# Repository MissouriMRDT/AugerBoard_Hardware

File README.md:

# AugerBoard_Hardware
KiCAD design files for Auger motion control board.

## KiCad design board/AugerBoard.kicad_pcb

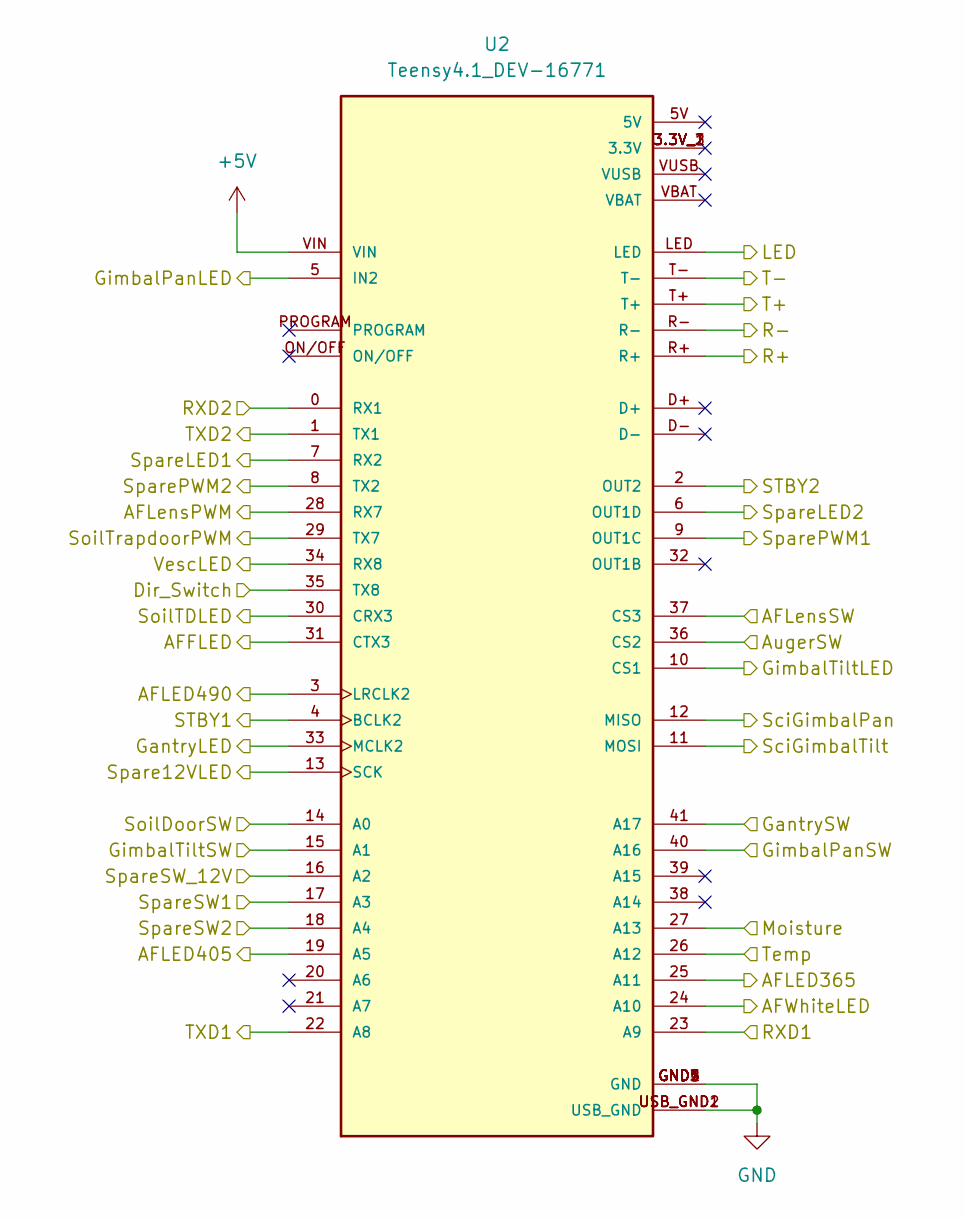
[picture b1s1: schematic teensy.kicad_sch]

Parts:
U2: Teensy4.1_DEV-16771; Teensy_4_1_Ethernet; PARTREV 4.1

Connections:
+5V: U2.VIN; also elsewhere on the board
/AF interface/AFLED365: U2.25 (A11); also elsewhere on the board
/AF interface/AFLED405: U2.19 (A5); also elsewhere on the board
/AF interface/AFLED490: U2.3 (LRCLK2); also elsewhere on the board
/AF interface/AFWhiteLED: U2.24 (A10); also elsewhere on the board
/Communications/LED: U2.LED; also elsewhere on the board
/Communications/R+: U2.R+; also elsewhere on the board
/Communications/R-: U2.R-; also elsewhere on the board
/Communications/RXD1: U2.23 (A9); also elsewhere on the board
/Communications/RXD2: U2.0 (RX1); also elsewhere on the board
/Communications/STBY1: U2.4 (BCLK2); also elsewhere on the board
/Communications/STBY2: U2.2 (OUT2); also elsewhere on the board
/Communications/T+: U2.T+; also elsewhere on the board
/Communications/T-: U2.T-; also elsewhere on the board
/Communications/TXD1: U2.22 (A8); also elsewhere on the board
/Communications/TXD2: U2.1 (TX1); also elsewhere on the board
/Power/AFFLED: U2.31 (CTX3); also elsewhere on the board
/Power/GantryLED: U2.33 (MCLK2); also elsewhere on the board
/Power/GimbalPanLED: U2.5 (IN2); also elsewhere on the board
/Power/GimbalTiltLED: U2.10 (CS1); also elsewhere on the board
/Power/SoilTDLED: U2.30 (CRX3); also elsewhere on the board
/Power/Spare12VLED: U2.13 (SCK); also elsewhere on the board
/Power/SpareLED1: U2.7 (RX2); also elsewhere on the board
/Power/SpareLED2: U2.6 (OUT1D); also elsewhere on the board
/Power/VescLED: U2.34 (RX8); also elsewhere on the board
/Servos/AFLensPWM: U2.28 (RX7); also elsewhere on the board
/Servos/SciGimbalPan: U2.12 (MISO); also elsewhere on the board
/Servos/SciGimbalTilt: U2.11 (MOSI); also elsewhere on the board
/Servos/SoilTrapdoorPWM: U2.29 (TX7); also elsewhere on the board
/Servos/SparePWM1: U2.9 (OUT1C); also elsewhere on the board
/Servos/SparePWM2: U2.8 (TX2); also elsewhere on the board
/Soil Sensors/Moisture: U2.27 (A13); also elsewhere on the board
/Soil Sensors/Temp: U2.26 (A12); also elsewhere on the board
/Teensy/AFLensSW: U2.37 (CS3); also elsewhere on the board
/Teensy/AugerSW: U2.36 (CS2); also elsewhere on the board
/Teensy/Dir_Switch: U2.35 (TX8); also elsewhere on the board
/Teensy/GantrySW: U2.41 (A17); also elsewhere on the board
/Teensy/GimbalPanSW: U2.40 (A16); also elsewhere on the board
/Teensy/GimbalTiltSW: U2.15 (A1); also elsewhere on the board
/Teensy/SoilDoorSW: U2.14 (A0); also elsewhere on the board
/Teensy/SpareSW1: U2.17 (A3); also elsewhere on the board
/Teensy/SpareSW2: U2.18 (A4); also elsewhere on the board
/Teensy/SpareSW_12V: U2.16 (A2); also elsewhere on the board
GND: U2.GND1 (GND), U2.GND2 (GND), U2.GND3 (GND), U2.GND4 (GND), U2.GND5 (GND), U2.USB_GND1 (USB_GND), U2.USB_GND2 (USB_GND); also elsewhere on the board

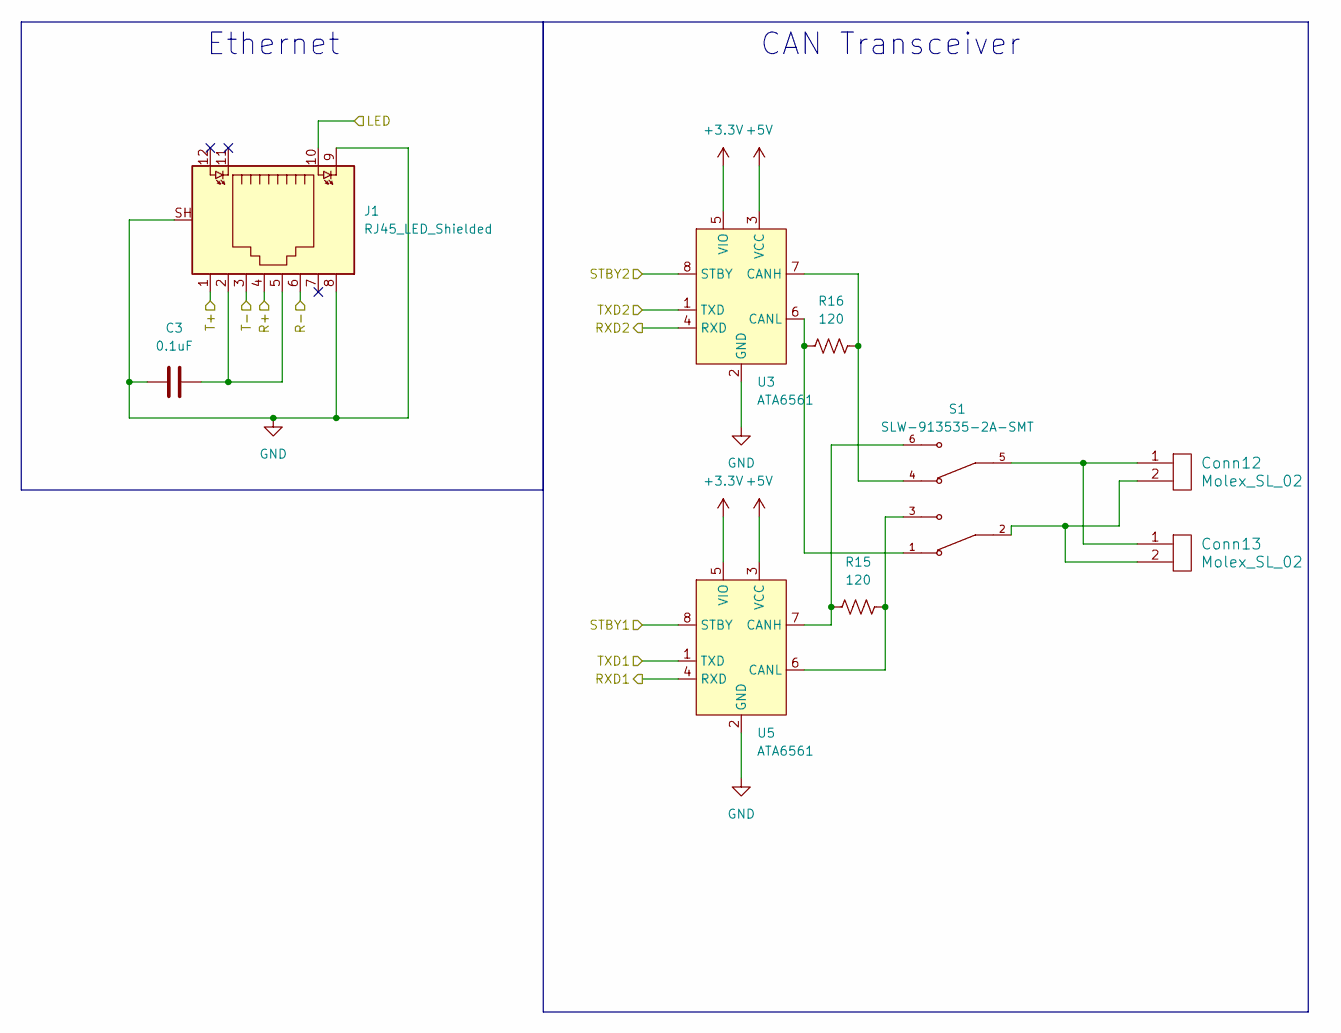
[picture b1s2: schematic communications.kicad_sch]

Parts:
C3: 0.1uF; C_0603_1608Metric_Pad1.08x0.95mm_HandSolder
Conn12, Conn13: Molex_SL_02; MOLEX_SL_02_Vertical
J1: RJ45_LED_Shielded; RJ45_Teensy
R15, R16: 120; R_0603_1608Metric_Pad0.98x0.95mm_HandSolder
S1: SLW-913535-2A-SMT; SW_SLW-913535-2A-SMT; PARTREV 1.01
U3, U5: ATA6561; SOIC-8_3.9x4.9mm_P1.27mm

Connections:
+3.3V: U3.5 (VIO), U5.5 (VIO); also elsewhere on the board
+5V: U3.3 (VCC), U5.3 (VCC); also elsewhere on the board
/Communications/LED: J1.10; also elsewhere on the board
/Communications/R+: J1.4; also elsewhere on the board
/Communications/R-: J1.6; also elsewhere on the board
/Communications/RXD1: U5.4 (RXD); also elsewhere on the board
/Communications/RXD2: U3.4 (RXD); also elsewhere on the board
/Communications/STBY1: U5.8 (STBY); also elsewhere on the board
/Communications/STBY2: U3.8 (STBY); also elsewhere on the board
/Communications/T+: J1.1; also elsewhere on the board
/Communications/T-: J1.3; also elsewhere on the board
/Communications/TXD1: U5.1 (TXD); also elsewhere on the board
/Communications/TXD2: U3.1 (TXD); also elsewhere on the board
GND: C3.1, J1.8, J1.9, J1.SH, U3.2 (GND), U5.2 (GND); also elsewhere on the board
unnamed: C3.2, J1.2, J1.5
unnamed: Conn12.1, Conn13.1, S1.5
unnamed: Conn12.2, Conn13.2, S1.2
unnamed: R16.1, S1.4, U3.7 (CANH)
unnamed: R16.2, S1.1, U3.6 (CANL)
unnamed: R15.2, S1.6, U5.7 (CANH)
unnamed: R15.1, S1.3, U5.6 (CANL)

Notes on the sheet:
Ethernet
CAN Transceiver

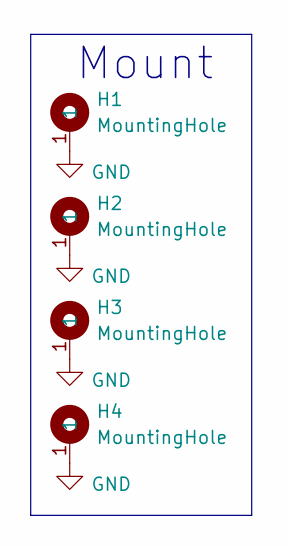
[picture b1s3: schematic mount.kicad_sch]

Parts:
H1, H2, H3, H4: MountingHole; 4_40_Hole_Pad_Via

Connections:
GND: H1.1, H2.1, H3.1, H4.1; also elsewhere on the board

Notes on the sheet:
Mount

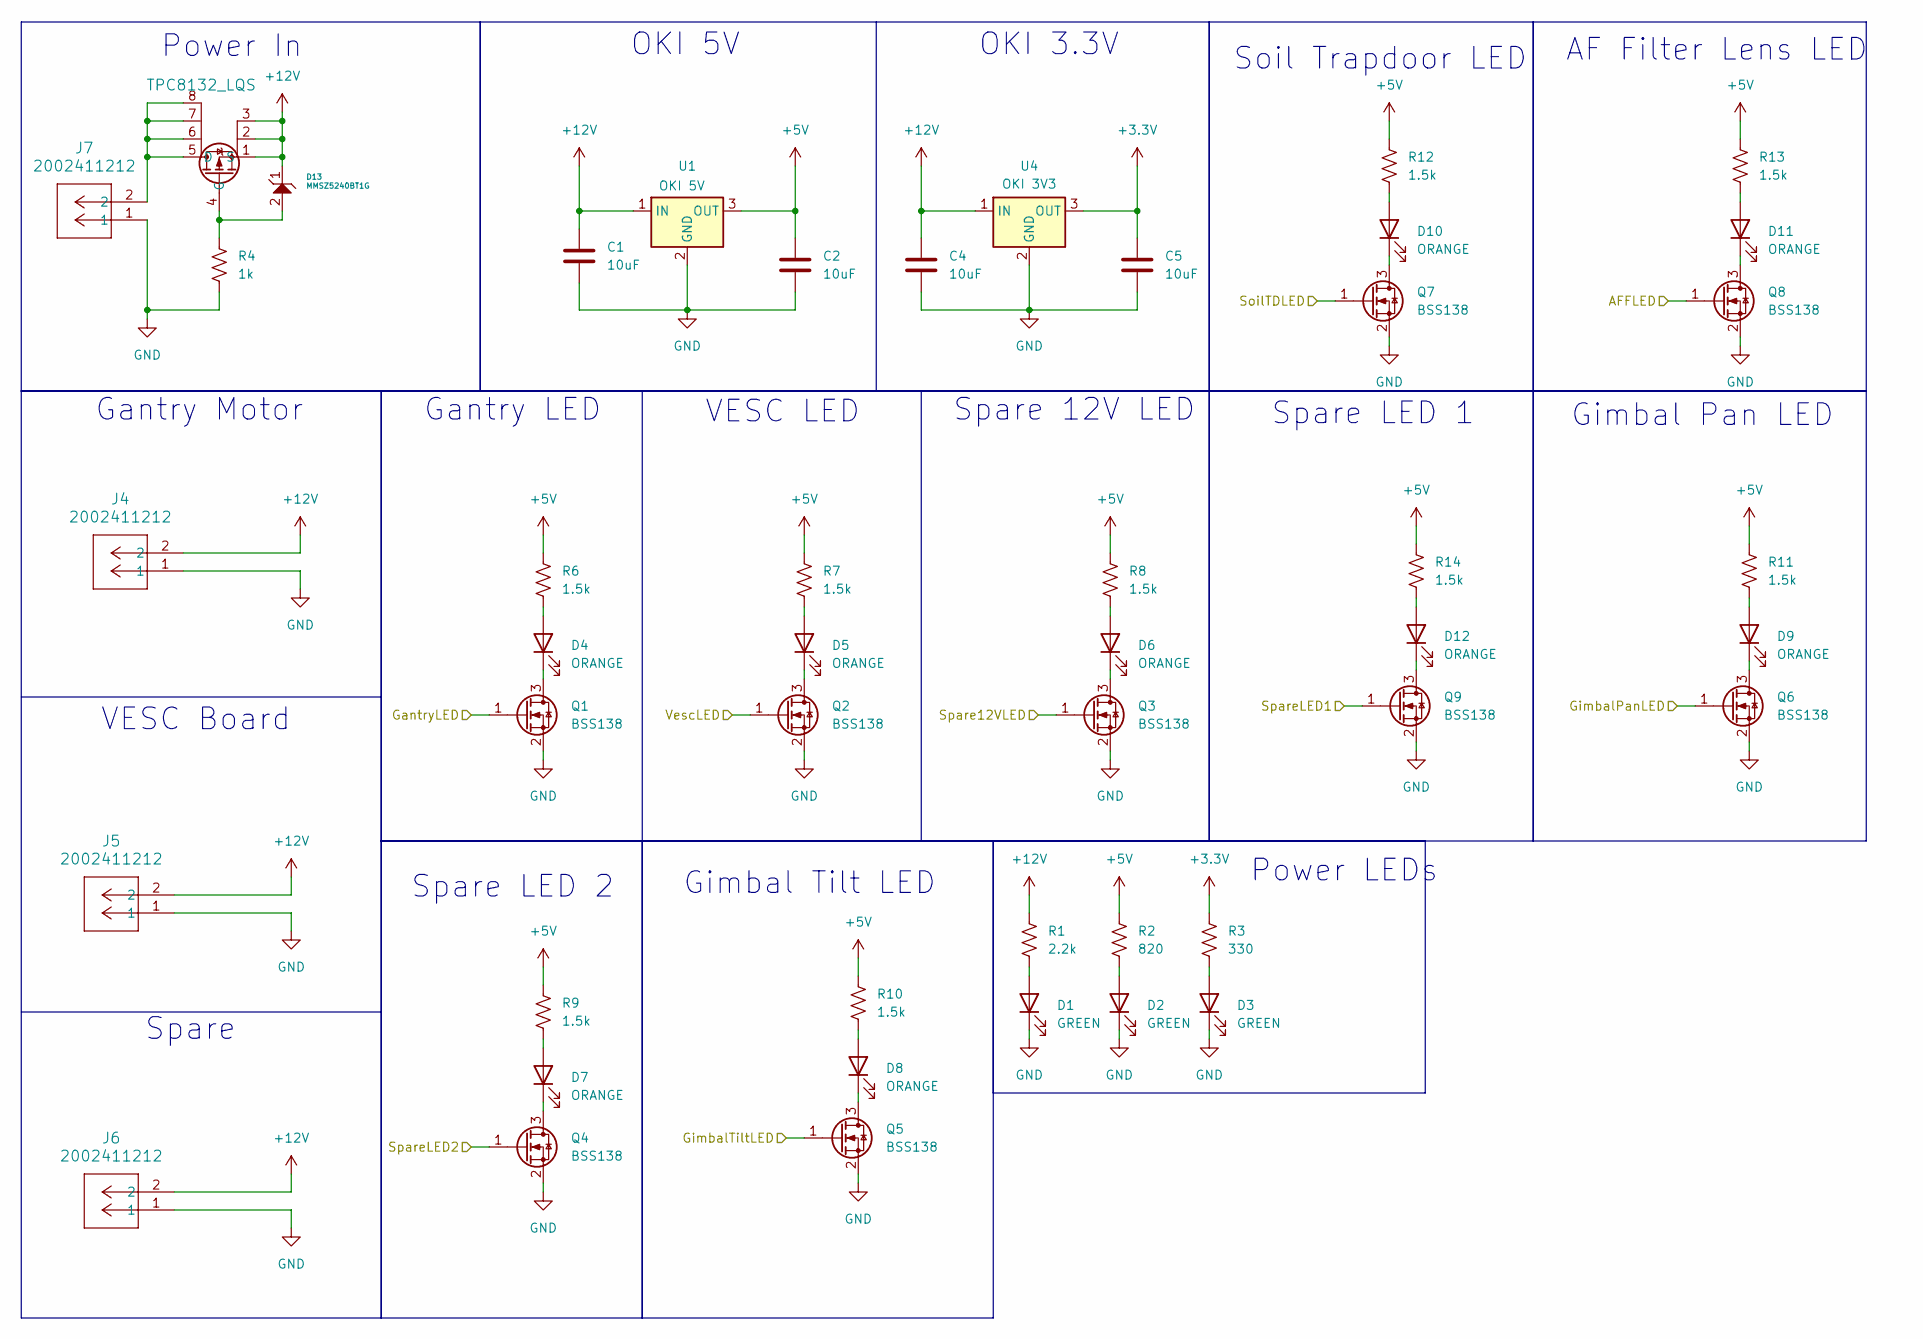
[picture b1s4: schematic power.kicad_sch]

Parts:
C1, C2, C4, C5: 10uF; C_0603_1608Metric_Pad1.08x0.95mm_HandSolder
D1, D2, D3: GREEN; LED_0603_1608Metric_Pad1.05x0.95mm_HandSolder
D4, D5, D6, D7, D8, D9, D10, D11, D12: ORANGE; LED_0603_1608Metric_Pad1.05x0.95mm_HandSolder
D13: MMSZ5240BT1G; SOD-123_ONS-L
J4, J5, J6, J7: 2002411212; CONN_SD-76825-0100_02_MOL
MOSFET1: TPC8132_LQS; SOP-8_TOS-L
Q1, Q2, Q3, Q4, Q5, Q6, Q7, Q8, Q9: BSS138; SOT-23
R1: 2.2k; R_0603_1608Metric_Pad0.98x0.95mm_HandSolder
R2: 820; R_0603_1608Metric_Pad0.98x0.95mm_HandSolder
R3: 330; R_0603_1608Metric_Pad0.98x0.95mm_HandSolder
R4: 1k; R_0603_1608Metric_Pad0.98x0.95mm_HandSolder
R6, R7, R8, R9, R10, R11, R12, R13, R14: 1.5k; R_0603_1608Metric_Pad0.98x0.95mm_HandSolder
U1: OKI 5V; OKI_Horizontal
U4: OKI 3V3; OKI_Horizontal

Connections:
+3.3V: C5.1, R3.1, U4.3 (OUT); also elsewhere on the board
+5V: C2.1, R2.1, R6.1, R7.1, R8.1, R9.1, R10.1, R11.1, R12.1, R13.1, R14.1, U1.3 (OUT); also elsewhere on the board
+12V: C1.1, C4.1, D13.1, J4.2, J5.2, J6.2, MOSFET1.1 (S), MOSFET1.2, MOSFET1.3, R1.1, U1.1 (IN), U4.1 (IN); also elsewhere on the board
/Power/AFFLED: Q8.1 (G); also elsewhere on the board
/Power/GantryLED: Q1.1 (G); also elsewhere on the board
/Power/GimbalPanLED: Q6.1 (G); also elsewhere on the board
/Power/GimbalTiltLED: Q5.1 (G); also elsewhere on the board
/Power/SoilTDLED: Q7.1 (G); also elsewhere on the board
/Power/Spare12VLED: Q3.1 (G); also elsewhere on the board
/Power/SpareLED1: Q9.1 (G); also elsewhere on the board
/Power/SpareLED2: Q4.1 (G); also elsewhere on the board
/Power/VescLED: Q2.1 (G); also elsewhere on the board
GND: C1.2, C2.2, C4.2, C5.2, D1.1 (K), D2.1 (K), D3.1 (K), J4.1, J5.1, J6.1, J7.1, Q1.2 (S), Q2.2 (S), Q3.2 (S), Q4.2 (S), Q5.2 (S), Q6.2 (S), Q7.2 (S), Q8.2 (S), Q9.2 (S), R4.2, U1.2 (GND), U4.2 (GND); also elsewhere on the board
unnamed: D1.2 (A), R1.2
unnamed: D2.2 (A), R2.2
unnamed: D3.2 (A), R3.2
unnamed: D4.2 (A), R6.2
unnamed: D4.1 (K), Q1.3 (D)
unnamed: D5.2 (A), R7.2
unnamed: D5.1 (K), Q2.3 (D)
unnamed: D6.2 (A), R8.2
unnamed: D6.1 (K), Q3.3 (D)
unnamed: D7.2 (A), R9.2
unnamed: D7.1 (K), Q4.3 (D)
unnamed: D8.2 (A), R10.2
unnamed: D8.1 (K), Q5.3 (D)
unnamed: D9.2 (A), R11.2
unnamed: D9.1 (K), Q6.3 (D)
unnamed: D10.2 (A), R12.2
unnamed: D10.1 (K), Q7.3 (D)
unnamed: D11.2 (A), R13.2
unnamed: D11.1 (K), Q8.3 (D)
unnamed: D12.2 (A), R14.2
unnamed: D12.1 (K), Q9.3 (D)
unnamed: J7.2, MOSFET1.5 (D), MOSFET1.6, MOSFET1.7, MOSFET1.8
unnamed: D13.2, MOSFET1.4 (G), R4.1

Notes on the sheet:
Power In
Spare 12V LED
VESC LED
Gimbal Tilt LED
Spare LED 1
OKI 3.3V
Gantry Motor
AF Filter Lens LED
Power LEDs
Spare LED 2
Gantry LED
Soil Trapdoor LED
Gimbal Pan LED
OKI 5V
Spare
VESC Board

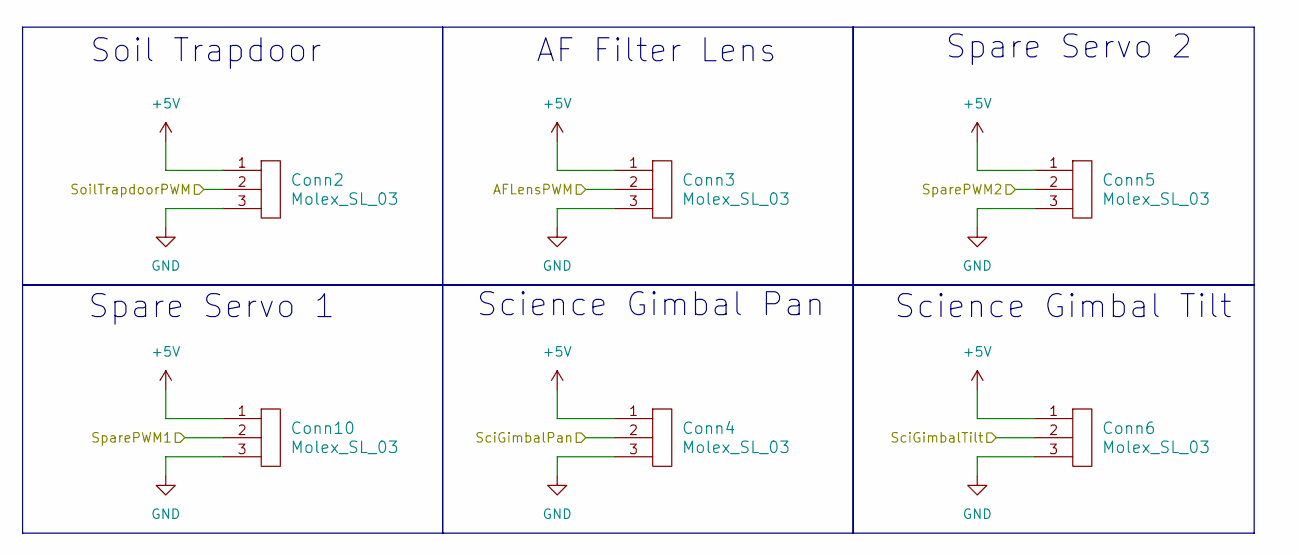
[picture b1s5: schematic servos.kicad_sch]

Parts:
Conn2, Conn3, Conn4, Conn5, Conn6, Conn10: Molex_SL_03; MOLEX_SL_03_Vertical

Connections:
+5V: Conn2.1, Conn3.1, Conn4.1, Conn5.1, Conn6.1, Conn10.1; also elsewhere on the board
/Servos/AFLensPWM: Conn3.2; also elsewhere on the board
/Servos/SciGimbalPan: Conn4.2; also elsewhere on the board
/Servos/SciGimbalTilt: Conn6.2; also elsewhere on the board
/Servos/SoilTrapdoorPWM: Conn2.2; also elsewhere on the board
/Servos/SparePWM1: Conn10.2; also elsewhere on the board
/Servos/SparePWM2: Conn5.2; also elsewhere on the board
GND: Conn2.3, Conn3.3, Conn4.3, Conn5.3, Conn6.3, Conn10.3; also elsewhere on the board

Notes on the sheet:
AF Filter Lens
Soil Trapdoor
Spare Servo 1
Spare Servo 2
Science Gimbal Pan
Science Gimbal Tilt

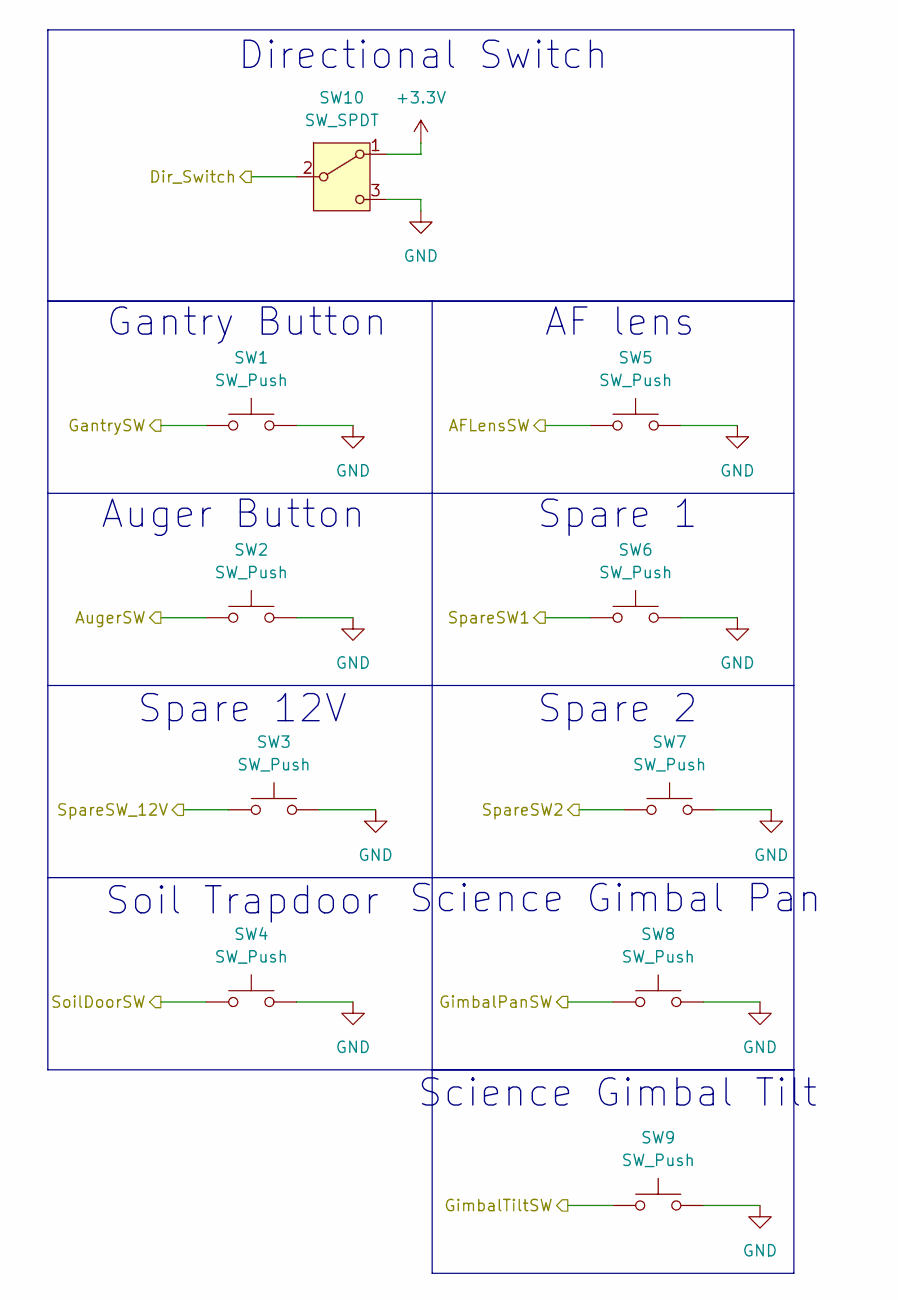
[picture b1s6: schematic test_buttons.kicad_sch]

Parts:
SW1, SW2, SW3, SW4, SW5, SW6, SW7, SW8, SW9: SW_Push; SW_SPST_TL3305A
SW10: SW_SPDT; SW_Slide_SPDT_Straight_CK_OS102011MS2Q

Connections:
+3.3V: SW10.1 (A); also elsewhere on the board
/Teensy/AFLensSW: SW5.1; also elsewhere on the board
/Teensy/AugerSW: SW2.1; also elsewhere on the board
/Teensy/Dir_Switch: SW10.2 (B); also elsewhere on the board
/Teensy/GantrySW: SW1.1; also elsewhere on the board
/Teensy/GimbalPanSW: SW8.1; also elsewhere on the board
/Teensy/GimbalTiltSW: SW9.1; also elsewhere on the board
/Teensy/SoilDoorSW: SW4.1; also elsewhere on the board
/Teensy/SpareSW1: SW6.1; also elsewhere on the board
/Teensy/SpareSW2: SW7.1; also elsewhere on the board
/Teensy/SpareSW_12V: SW3.1; also elsewhere on the board
GND: SW1.2, SW2.2, SW3.2, SW4.2, SW5.2, SW6.2, SW7.2, SW8.2, SW9.2, SW10.3 (C); also elsewhere on the board

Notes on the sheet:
Spare 2
Spare 1
Directional Switch
Gantry Button
Auger Button
Spare 12V
Science Gimbal Pan
AF lens
Soil Trapdoor
Science Gimbal Tilt

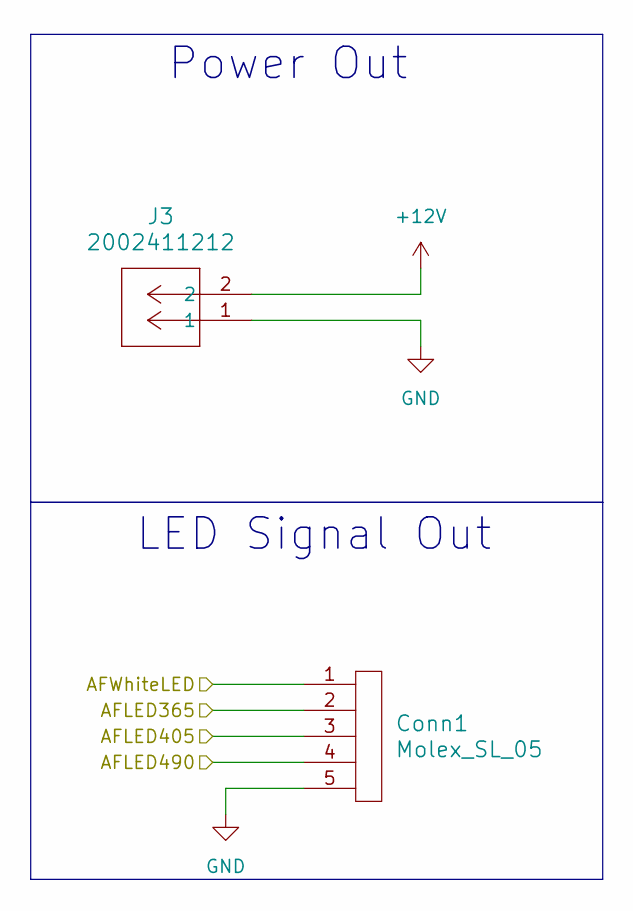
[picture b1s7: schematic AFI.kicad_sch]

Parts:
Conn1: Molex_SL_05; MOLEX_SL_05_Vertical
J3: 2002411212; CONN_SD-76825-0100_02_MOL

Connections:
+12V: J3.2; also elsewhere on the board
/AF interface/AFLED365: Conn1.2; also elsewhere on the board
/AF interface/AFLED405: Conn1.3; also elsewhere on the board
/AF interface/AFLED490: Conn1.4; also elsewhere on the board
/AF interface/AFWhiteLED: Conn1.1; also elsewhere on the board
GND: Conn1.5, J3.1; also elsewhere on the board

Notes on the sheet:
LED Signal Out
Power Out

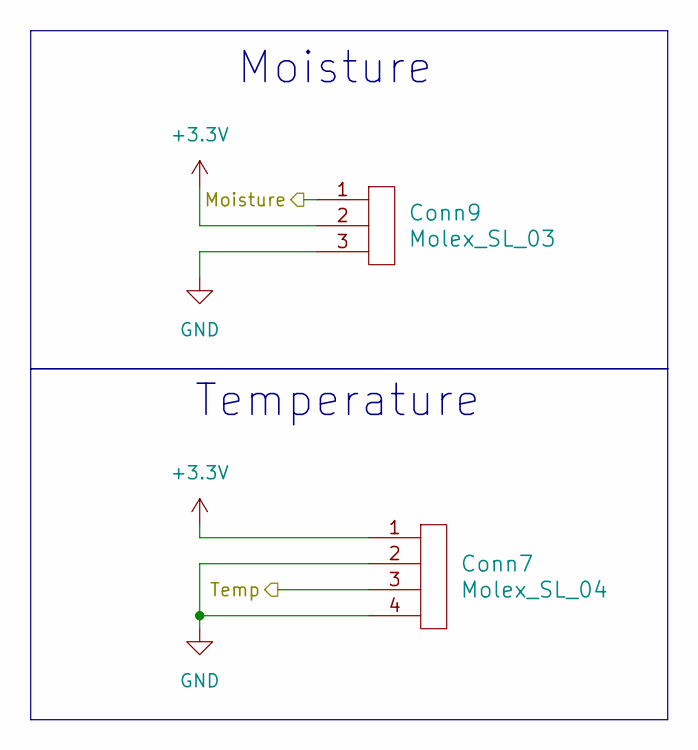
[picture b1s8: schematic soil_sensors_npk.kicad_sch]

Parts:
Conn7: Molex_SL_04; MOLEX_SL_04_Vertical
Conn9: Molex_SL_03; MOLEX_SL_03_Vertical

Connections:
+3.3V: Conn7.1, Conn9.2; also elsewhere on the board
/Soil Sensors/Moisture: Conn9.1; also elsewhere on the board
/Soil Sensors/Temp: Conn7.3; also elsewhere on the board
GND: Conn7.2, Conn7.4, Conn9.3; also elsewhere on the board

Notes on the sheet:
Moisture
Temperature

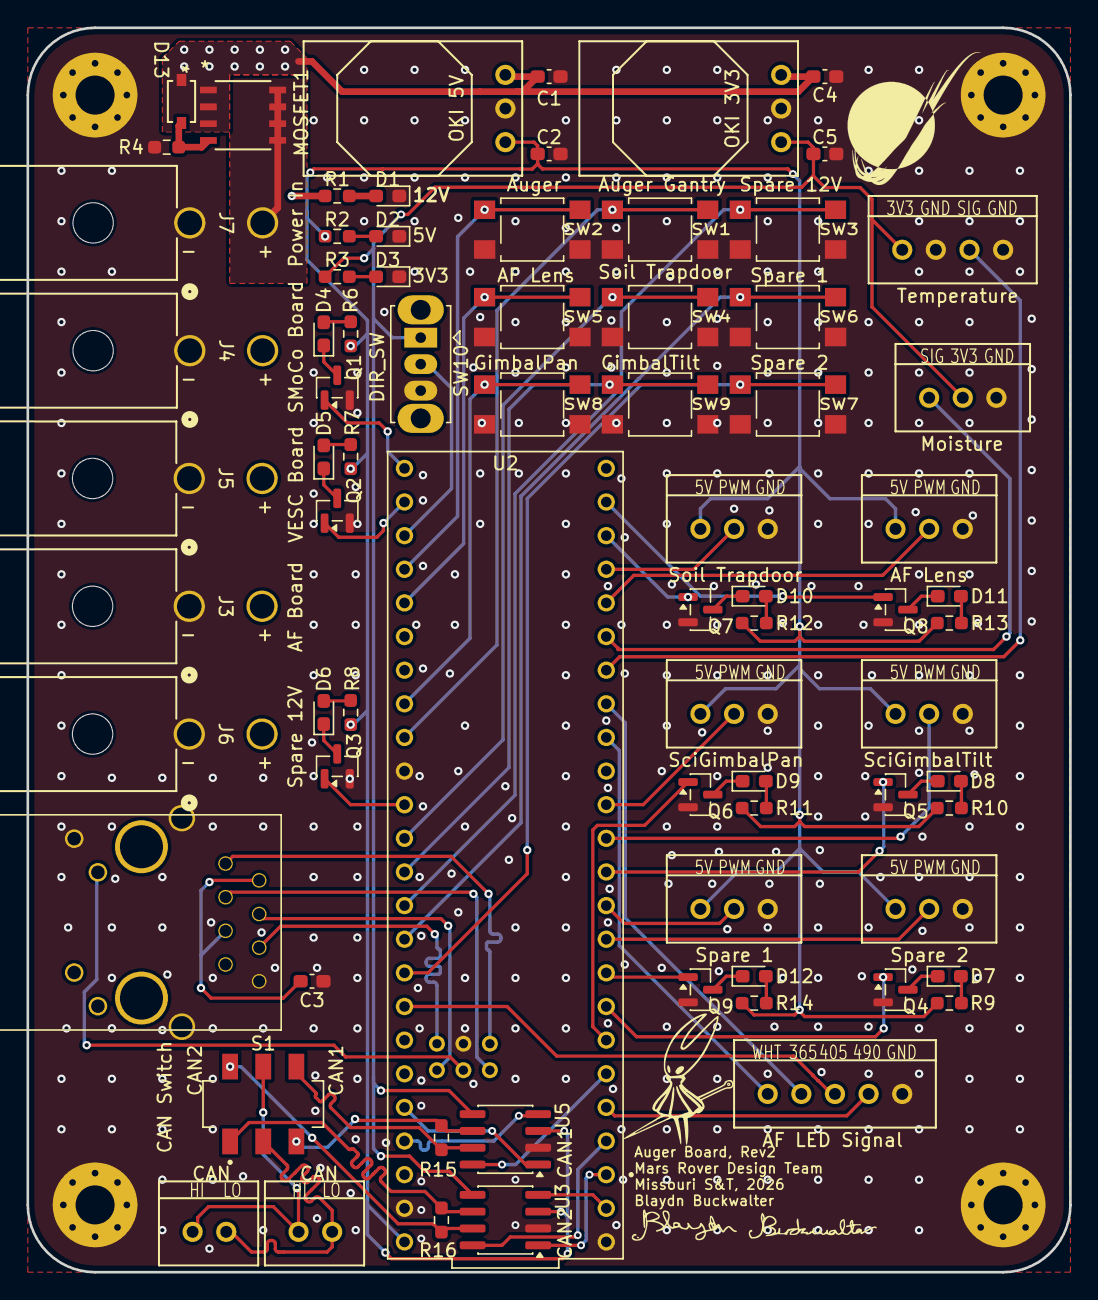
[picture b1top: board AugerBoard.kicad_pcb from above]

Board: 2 copper layers, 78.7 x 94.0 mm, 80 parts (0 on the bottom side), 76 nets.

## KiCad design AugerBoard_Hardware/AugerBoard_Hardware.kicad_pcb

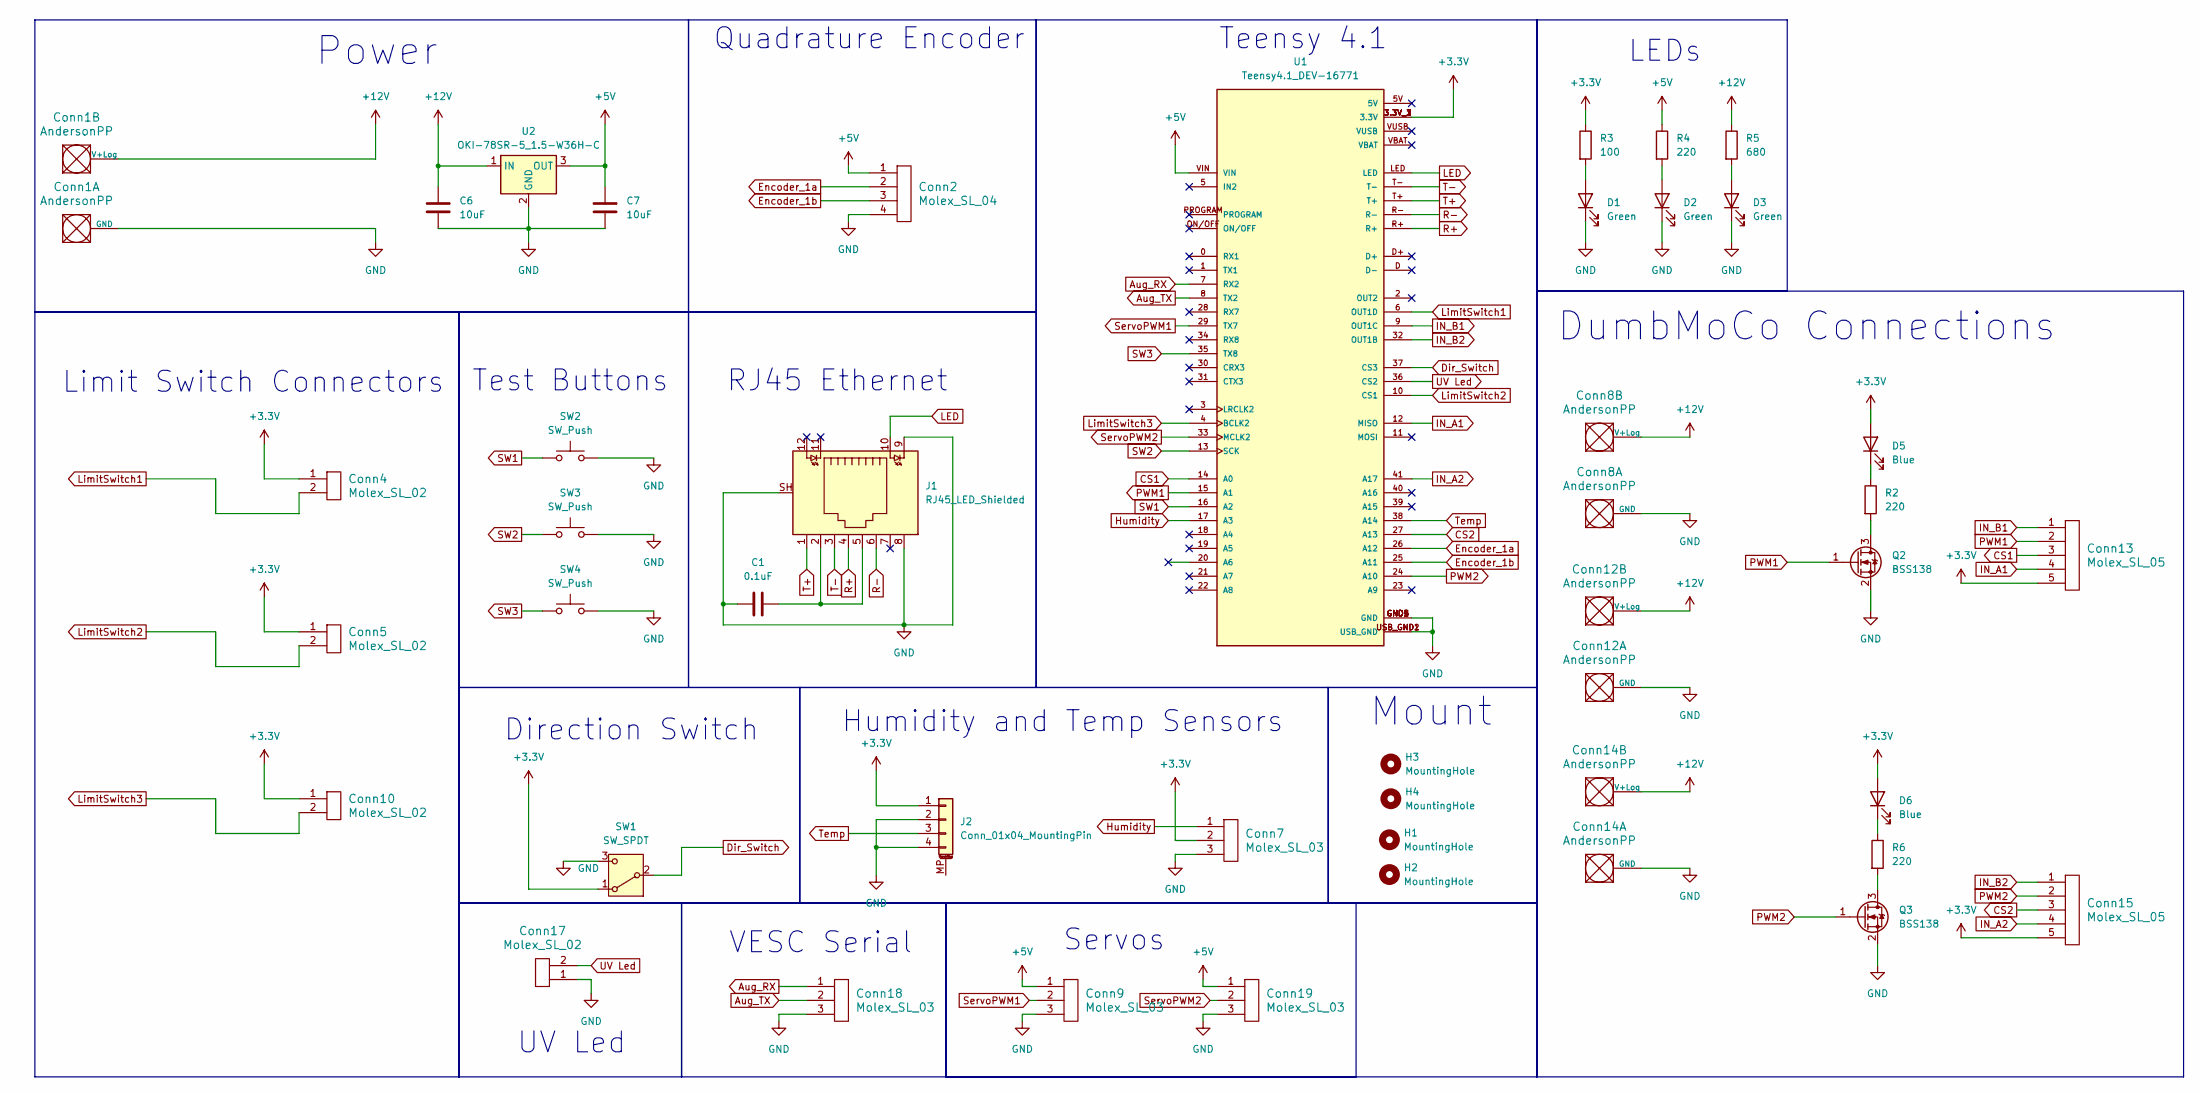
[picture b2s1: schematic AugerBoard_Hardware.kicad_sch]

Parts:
C1: 0.1uF; C_0603_1608Metric_Pad1.08x0.95mm_HandSolder
C6, C7: 10uF; C_0603_1608Metric_Pad1.08x0.95mm_HandSolder
Conn1, Conn8, Conn12, Conn14: AndersonPP; Square_Anderson_2_H_Side_By_Side
Conn2: Molex_SL_04; MOLEX_SL_04_Vertical
Conn4, Conn5, Conn10, Conn17: Molex_SL_02; MOLEX_SL_02_Vertical
Conn7, Conn9, Conn18, Conn19: Molex_SL_03; MOLEX_SL_03_Vertical
Conn13, Conn15: Molex_SL_05; MOLEX_SL_05_Vertical
D1, D2, D3: Green; LED_0603_1608Metric_Pad1.05x0.95mm_HandSolder
D5, D6: Blue; LED_0603_1608Metric_Pad1.05x0.95mm_HandSolder
H1, H2, H3, H4: MountingHole; 4_40_Hole_Corner
J1: RJ45_LED_Shielded; RJ45_Teensy
J2: Conn_01x04_MountingPin; PinHeader_1x04_P2.54mm_Vertical
Q2, Q3: BSS138; SOT-23
R2, R4, R6: 220; R_0603_1608Metric_Pad0.98x0.95mm_HandSolder
R3: 100; R_0603_1608Metric_Pad0.98x0.95mm_HandSolder
R5: 680; R_0603_1608Metric_Pad0.98x0.95mm_HandSolder
SW1: SW_SPDT; SW_Slide_SPDT_Straight_CK_OS102011MS2Q
SW2, SW3, SW4: SW_Push; SW_SPST_TL3305A
U1: Teensy4.1_DEV-16771; Teensy_4_1_Ethernet; PARTREV 4.1
U2: OKI-78SR-5_1.5-W36H-C; Converter_DCDC_Murata_OKI-78SR_Horizontal

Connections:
+3.3V: Conn4.1, Conn5.1, Conn7.2, Conn10.1, Conn13.5, Conn15.5, D5.2 (A), D6.2 (A), J2.1, R3.1, SW1.1 (A), U1.3.3V_1 (3.3V), U1.3.3V_2 (3.3V), U1.3.3V_3 (3.3V)
+5V: C7.1, Conn2.1, Conn9.1, Conn19.1, R4.1, U1.VIN, U2.3 (OUT)
+12V: C6.1, Conn1.2 (V+Log), Conn8.2 (V+Log), Conn12.2 (V+Log), Conn14.2 (V+Log), R5.1, U2.1 (IN)
Aug_RX: Conn18.1, U1.7 (RX2)
Aug_TX: Conn18.2, U1.8 (TX2)
CS1: Conn13.3, U1.14 (A0)
CS2: Conn15.3, U1.27 (A13)
Dir_Switch: SW1.2 (B), U1.37 (CS3)
Encoder_1a: Conn2.2, U1.26 (A12)
Encoder_1b: Conn2.3, U1.25 (A11)
GND: C1.1, C6.2, C7.2, Conn1.1 (GND), Conn2.4, Conn7.3, Conn8.1 (GND), Conn9.3, Conn12.1 (GND), Conn14.1 (GND), Conn17.1, Conn18.3, Conn19.3, D1.1 (K), D2.1 (K), D3.1 (K), J1.8, J1.9, J1.SH, J2.2, J2.4, Q2.2 (S), Q3.2 (S), SW1.3 (C), SW2.2, SW3.2, SW4.2, U1.GND1 (GND), U1.GND2 (GND), U1.GND3 (GND), U1.GND4 (GND), U1.GND5 (GND), U1.USB_GND1 (USB_GND), U1.USB_GND2 (USB_GND), U2.2 (GND)
Humidity: Conn7.1, U1.17 (A3)
IN_A1: Conn13.4, U1.12 (MISO)
IN_A2: Conn15.4, U1.41 (A17)
IN_B1: Conn13.1, U1.9 (OUT1C)
IN_B2: Conn15.1, U1.32 (OUT1B)
LED: J1.10, U1.LED
LimitSwitch1: Conn4.2, U1.6 (OUT1D)
LimitSwitch2: Conn5.2, U1.10 (CS1)
LimitSwitch3: Conn10.2, U1.4 (BCLK2)
unnamed: C1.2, J1.2, J1.5
unnamed: D1.2 (A), R3.2
unnamed: D2.2 (A), R4.2
unnamed: D3.2 (A), R5.2
unnamed: D5.1 (K), R2.1
unnamed: D6.1 (K), R6.1
unnamed: Q2.3 (D), R2.2
unnamed: Q3.3 (D), R6.2
PWM1: Conn13.2, Q2.1 (G), U1.15 (A1)
PWM2: Conn15.2, Q3.1 (G), U1.24 (A10)
R+: J1.4, U1.R+
R-: J1.6, U1.R-
SW1: SW2.1, U1.16 (A2)
SW2: SW3.1, U1.13 (SCK)
SW3: SW4.1, U1.35 (TX8)
ServoPWM1: Conn9.2, U1.29 (TX7)
ServoPWM2: Conn19.2, U1.33 (MCLK2)
T+: J1.1, U1.T+
T-: J1.3, U1.T-
Temp: J2.3, U1.38 (A14)
UV Led: Conn17.2, U1.36 (CS2)

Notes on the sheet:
Teensy 4.1
Quadrature Encoder
VESC Serial
Limit Switch Connectors
Test Buttons
UV Led
DumbMoCo Connections
Power
RJ45 Ethernet
Mount
LEDs
Humidity and Temp Sensors
Direction Switch
Servos
